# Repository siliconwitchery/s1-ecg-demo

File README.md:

# S1 ECG Reference Kit

**Features:**

- Single chip frontend based on the [AD8233](https://www.analog.com/en/products/ad8233.html)
- S1 Module with Bluetooth 5.2 and FPGA
- Integrated lithium battery
- Ultra low power auto-sleep down to 175uA
- Open source design

**Applications:**

- Learning and teaching around heart health
- Research of ML based ECG algorithms
- Wireless ECG data logging
- New product development

A powerful analog frontend combined with the S1 Module makes this an all-in-one kit to deploy and test algorithms with ease. Be that for learning, research, or as the starting point for your next product.

<br>

<br>

## Get the hardware

**Order the S1 ECG Kit from [Digi-Key](https://www.digikey.com/en/products/detail/silicon-witchery/S1-ECG-KIT/15926538) 🛍**

You're also free to build your own hardware using the design files in this repository. Everything is open source and ready to build upon.

- [Schematic](https://github.com/siliconwitchery/s1-ecg-demo/blob/main/schematic.pdf)
- [Gerber files](https://github.com/siliconwitchery/s1-ecg-demo/tree/main/gerber-files/factory-version)
- [Bill of materials](https://github.com/siliconwitchery/s1-ecg-demo/blob/main/bill-of-materials.pdf)

The design is produced in [KiCad v6.0.1](https://www.kicad.org/download/).

## Building the code

The S1 ECG reference kit uses a three probe measurement to determine heart activity. By holding the board with both hands, the device automatically wakes from sleep, and begins calibrating the amplifier sensitivity. After a few seconds, you will see your pulse displayed on the LED bar graph. Letting go of the terminals puts the system back into sleep mode.

The base firmware is highly expandable and a perfect starting point for new designs. To get started, begin by cloning this repository.

``` bash
git clone --recurse-submodules https://github.com/siliconwitchery/s1-ecg-demo.git
cd s1-ecg-demo
```

If you haven't already, set up these [tools](https://github.com/siliconwitchery/s1-sdk/blob/main/README.md#setting-up-the-tools) in order to build the project.

You should then be able to run `make`. *Be sure to include the path to your NRF SDK folder*.

``` bash
make -C firmware build-verilog NRF_SDK_PATH=${HOME}/nRF5_SDK
make -C firmware flash NRF_SDK_PATH=${HOME}/nRF5_SDK
```

The first `make` command will build the Verilog project, and convert the binary file into a header file. The nRF application transfers this binary to the FPGA after boot up. In your application, you could download this binary dynamically over Bluetooth rather than storing it within the flash of the nRF chip.

The second `make` command builds the nRF code, and flashes the module using a J-Link debugger. You can also use an [nRF52 devkit](https://www.nordicsemi.com/Products/Development-hardware/nrf52-dk), or [JLink Edu Mini](https://www.digikey.se/product-detail/en/segger-microcontroller-systems/8-08-91-J-LINK-EDU-MINI/899-1061-ND/7387472) along with and [this](https://www.tag-connect.com/product/tc2030-ctx-nl-6-pin-no-legs-cable-with-10-pin-micro-connector-for-cortex-processors) 6pin cable to flash your board.

Once you're up and running, you can begin customizing the application to your needs. Be sure to visit our documentation center to learn more about the S1 Module, as well as its features.

## Measuring sleep current

The board features a jumper disconnect to allow for the battery current to be directly measured. During sleep modes, this can be configured down to as low as 175uA or less, depending on the sleep state needed.

Note that if the USB-C power cable is plugged in while measuring, the charge current to the battery will be measured rather than the discharge current.

## Sensitivity of the ECG amplifier and EMI

The ECG amplifier is designed to pick up the tiny signals across your hands. It's therefore quite sensitive to external interference. Operation solely from the lithium battery is ideal. Here the board remains isolated from other noise sources and accurate measurements can be made.

Certain USB-C charges can induce a lot of EMI and ground loops can be created via the users hands. This may create noise in the measurement so it's worth keeping in mind when developing or logging data.

## Looking after the battery

**Lithium batteries are of course dangerous if improperly handled.** The S1 module features safety checks to avoid damage and such damage is unlikely. However it is possible to misconfigure the integrated power management IC to overcharge/undercharge or charge the lithium battery with too much current.

It is recommended to only use the battery configuration provided in this example to ensure safety and lifetime of the lithium battery.

If in doubt, it is possible to simply remove the battery current measurement jumper, and this will disconnect the battery from the system.

## Bugs and improvements

If you have any questions, or if something is unclear, feel free to create an [issue](https://github.com/siliconwitchery/s1-ecg-demo/issues) and we'll try our best to improve it.

## Licence

Copyright 2022 © Silicon Witchery.

This design is licenced under: [CERN Open Hardware Licence Version 2 - Permissive](https://ohwr.org/cern_ohl_p_v2.pdf).

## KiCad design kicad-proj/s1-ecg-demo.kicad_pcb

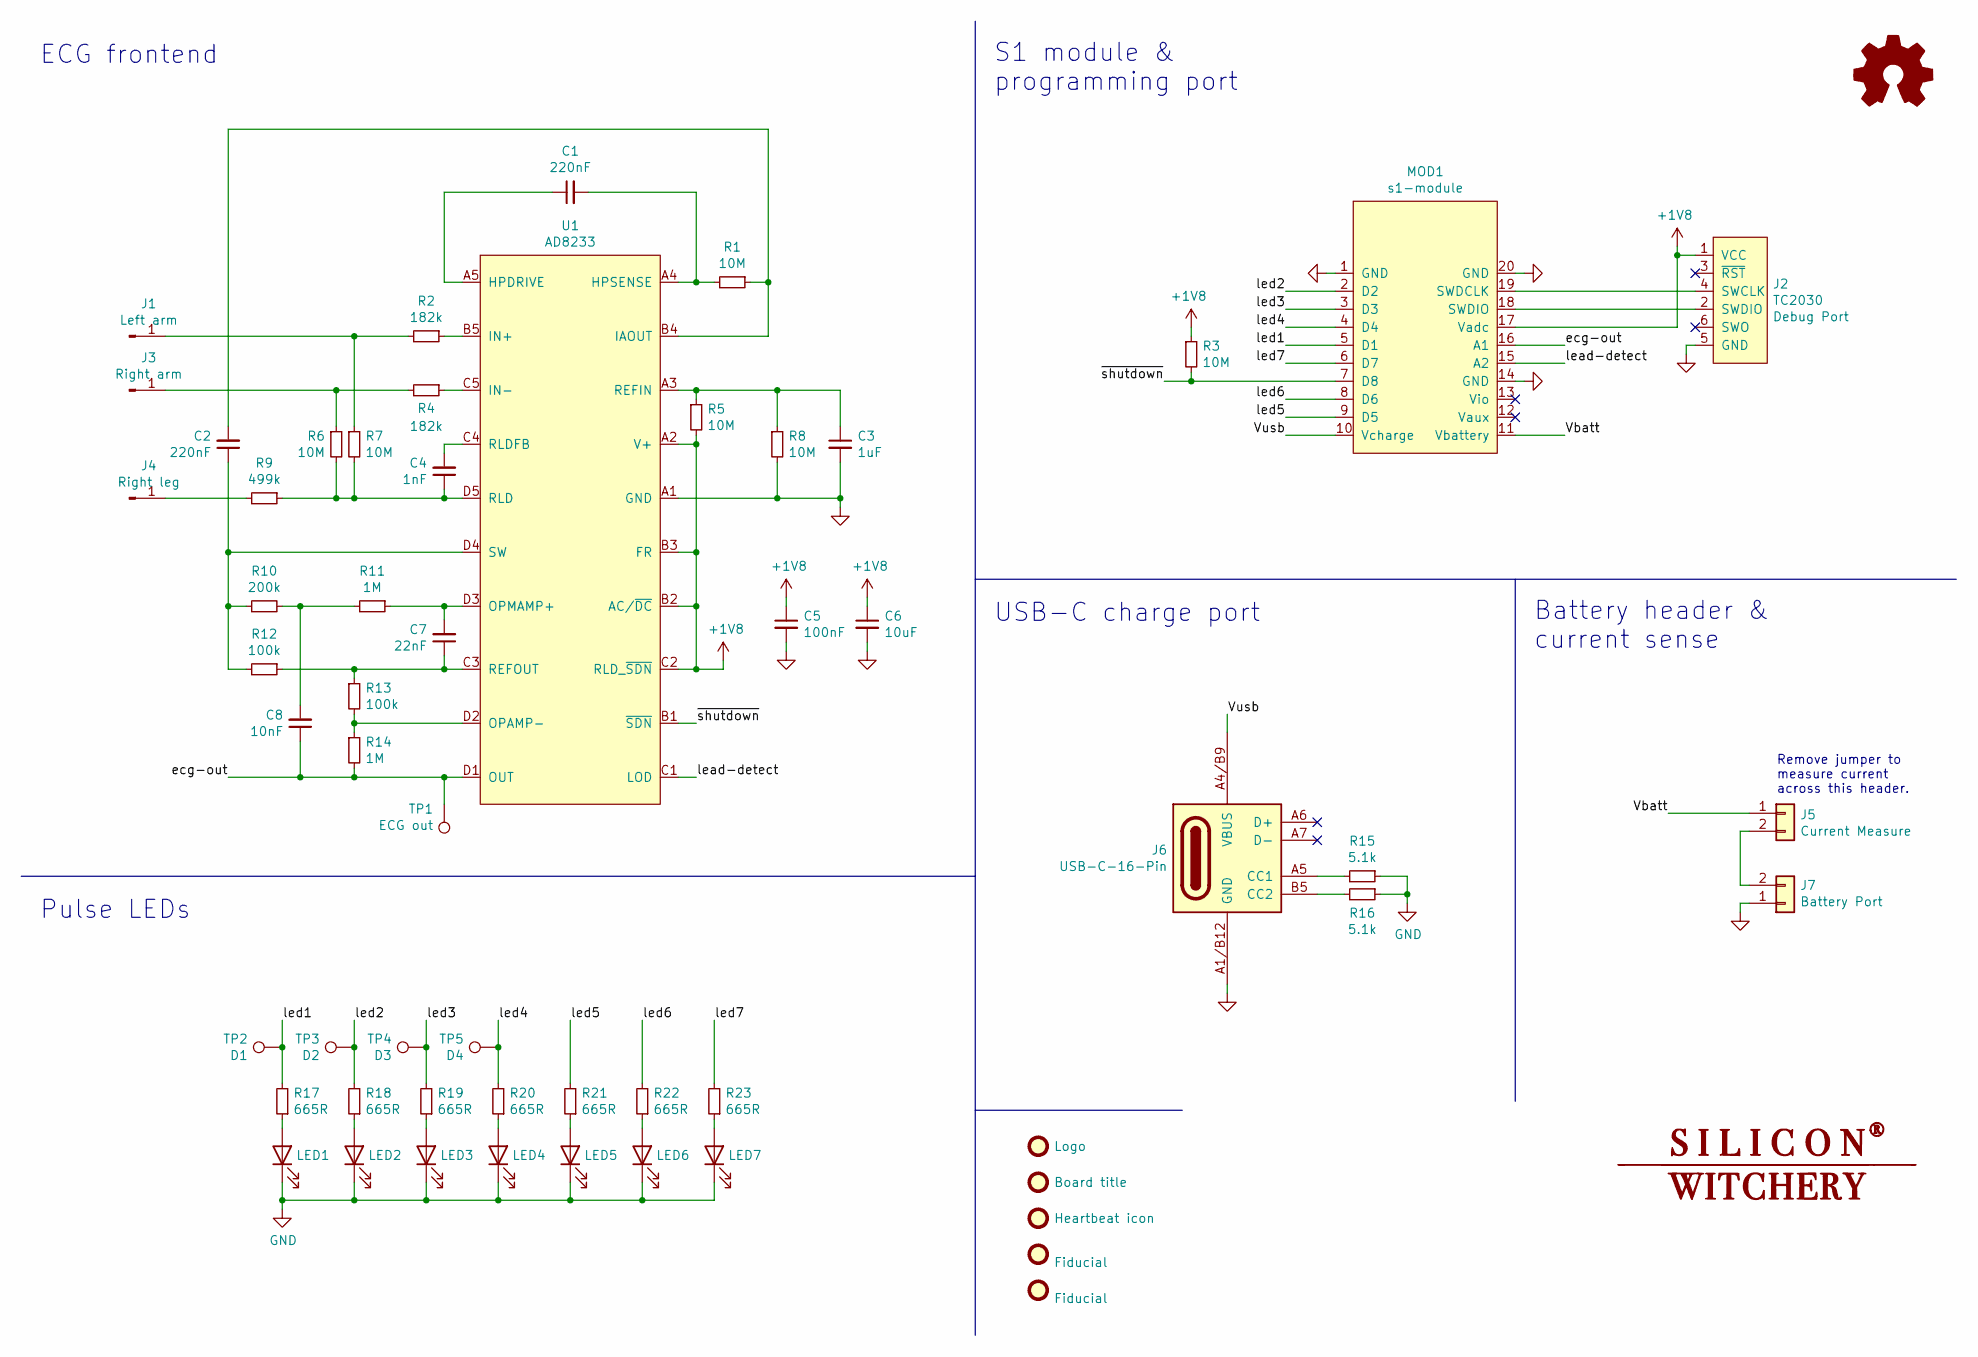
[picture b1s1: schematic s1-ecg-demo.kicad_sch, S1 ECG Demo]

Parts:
C1, C2: 220nF; C_0402_1005Metric
C3: 1uF; C_0402_1005Metric
C4: 1nF; C_0402_1005Metric
C5: 100nF; C_0402_1005Metric
C6: 10uF; C_0402_1005Metric
C7: 22nF; C_0402_1005Metric
C8: 10nF; C_0402_1005Metric
FID1: Logo; sw-logo
FID2: Board title; title
FID3: Heartbeat icon; heartbeat
FID4, FID5: Fiducial; Fiducial_0.5mm_Mask1mm
J1: Left arm; ECG-pad
J2: TC2030; Tag-Connect_TC2030-IDC-NL_2x03_P1.27mm_Vertical
J3: Right arm; ECG-pad
J4: Right leg; ECG-pad
J5: Current Measure; Conn_2_SMD_2.54mm
J6: USB-C-16-Pin; DX07S016JA1R1500
J7: Battery Port; Conn_2_SMD_2.54mm
LED1, LED2, LED3, LED4, LED5, LED6, LED7: LED; LED_0603_1608Metric
MOD1: s1-module
R1, R3, R5, R6, R7, R8: 10M; R_0201_0603Metric
R2, R4: 182k; R_0201_0603Metric
R9: 499k; R_0201_0603Metric
R10: 200k; R_0201_0603Metric
R11, R14: 1M; R_0201_0603Metric
R12, R13: 100k; R_0201_0603Metric
R15, R16: 5.1k; R_0201_0603Metric
R17, R18, R19, R20, R21, R22, R23: 665R; R_0201_0603Metric
TP1: ECG out; TestPoint_Pad_D1.0mm
TP2: D1; TestPoint_Pad_D1.0mm
TP3: D2; TestPoint_Pad_D1.0mm
TP4: D3; TestPoint_Pad_D1.0mm
TP5: D4; TestPoint_Pad_D1.0mm
U1: AD8233; WLCSP-20

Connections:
+1V8: C5.1, C6.1, J2.1 (VCC), MOD1.17 (Vadc), R3.1, R5.2, U1.A2 (V+), U1.B2 (AC/~DC), U1.B3 (FR), U1.C2 (RLD_~SDN)
/Vbatt: J5.1, MOD1.11 (Vbattery)
/ecg-out: C8.1, MOD1.16 (A1), R14.2, TP1.1, U1.D1 (OUT)
/lead-detect: MOD1.15 (A2), U1.C1 (LOD)
/led1: MOD1.5 (D1), R17.2, TP2.1
/led2: MOD1.2 (D2), R18.2, TP3.1
/led3: MOD1.3 (D3), R19.2, TP4.1
/led4: MOD1.4 (D4), R20.2, TP5.1
/led5: MOD1.9 (D5), R21.2
/led6: MOD1.8 (D6), R22.2
/led7: MOD1.6 (D7), R23.2
/~shutdown: MOD1.7 (D8), R3.2, U1.B1 (~SDN)
GND: C3.2, C5.2, C6.2, J2.5 (GND), J6.A1/B12 (GND), J6.A12/B1 (GND), J7.1, LED1.1 (K), LED2.1 (K), LED3.1 (K), LED4.1 (K), LED5.1 (K), LED6.1 (K), LED7.1 (K), MOD1.1 (GND), MOD1.14 (GND), MOD1.20 (GND), R8.2, R15.1, R16.1, U1.A1 (GND)
unnamed: C1.1, U1.A5 (HPDRIVE)
unnamed: C1.2, R1.2, U1.A4 (HPSENSE)
unnamed: C2.1, R10.1, R12.2, U1.D4 (SW)
unnamed: C2.2, R1.1, U1.B4 (IAOUT)
unnamed: C3.1, R5.1, R8.1, U1.A3 (REFIN)
unnamed: C4.1, R6.2, R7.2, R9.1, U1.D5 (RLD)
unnamed: C4.2, U1.C4 (RLDFB)
unnamed: C7.1, R12.1, R13.1, U1.C3 (REFOUT)
unnamed: C7.2, R11.1, U1.D3 (OPMAMP+)
unnamed: C8.2, R10.2, R11.2
unnamed: J1.1, R2.2, R7.1
unnamed: J2.2 (SWDIO), MOD1.18 (SWDIO)
unnamed: J2.4 (SWCLK), MOD1.19 (SWDCLK)
unnamed: J3.1, R4.2, R6.1
unnamed: J4.1, R9.2
unnamed: J5.2, J7.2
unnamed: J6.A5 (CC1), R15.2
unnamed: J6.B5 (CC2), R16.2
unnamed: LED1.2 (A), R17.1
unnamed: LED2.2 (A), R18.1
unnamed: LED3.2 (A), R19.1
unnamed: LED4.2 (A), R20.1
unnamed: LED5.2 (A), R21.1
unnamed: LED6.2 (A), R22.1
unnamed: LED7.2 (A), R23.1
unnamed: R2.1, U1.B5 (IN+)
unnamed: R4.1, U1.C5 (IN-)
unnamed: R13.2, R14.1, U1.D2 (OPAMP-)
VBUS: J6.A4/B9 (VBUS), J6.A9/B4 (VBUS), MOD1.10 (Vcharge)

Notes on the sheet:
Battery header & current sense
USB-C charge port
S1 module & programming port
ECG frontend
Remove jumper to measure current across this header.
Pulse LEDs

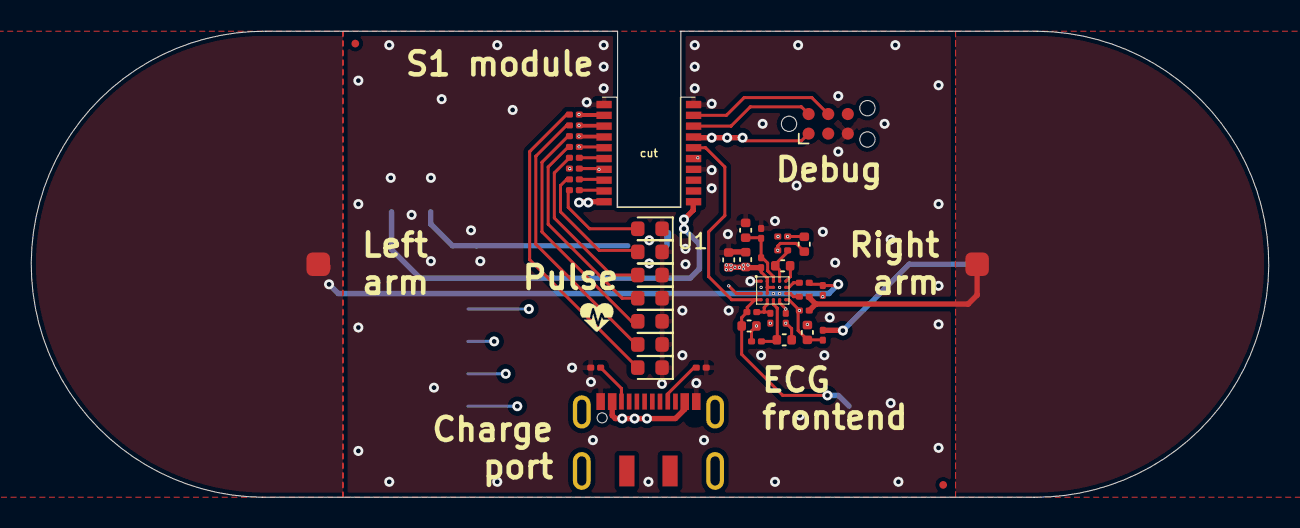
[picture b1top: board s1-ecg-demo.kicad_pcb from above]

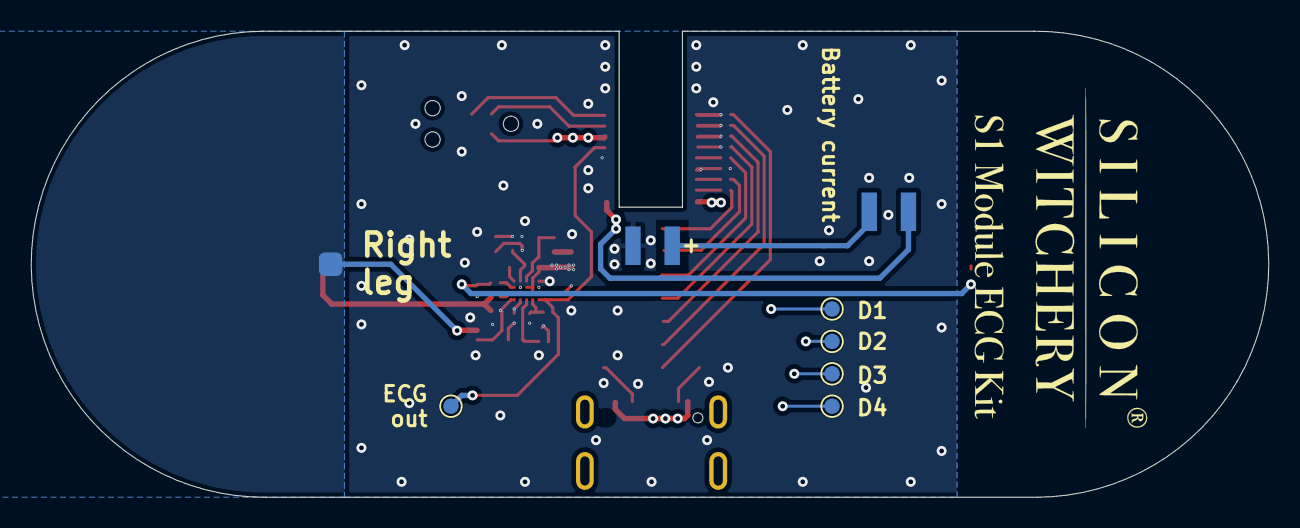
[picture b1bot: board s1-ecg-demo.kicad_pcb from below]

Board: 4 copper layers, 80.2 x 30.2 mm, 57 parts (10 on the bottom side), 42 nets.

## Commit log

2021-08-10 Initial
2021-08-10 added schematic
2021-08-10 added BOM
2021-08-12 Updated LEDs and BOM
2021-08-13 updated to match eval board
2021-08-16 pill shape, nearly done routing
2021-08-17 Layout complete, needs checking
2021-08-18 Final check done
2021-08-18 initial firmware
2021-08-18 removed submodule
2021-08-18 modified tasks to include paths
2021-08-18 readme
2021-08-18 end of day 18-08
2021-08-18 Little bit of clean up fixed battery and current header re-exported gerbers
2021-08-19 Final files ready for order
2021-08-19 Simple FIR filter works on ADC data
2021-08-20 SPI tx to fpga works
2021-08-20 1 pin pwm works
2021-08-23 Added factory gerber files
2021-08-26 ecg on led display is ok, auto sdn on leads off
2021-08-26 included s1-sdk changes
2021-08-27 temp
2021-08-27 added main.h
2021-08-27 formatting
2021-08-27 io extender temp
2021-08-31 New BOM added
2021-08-31 BOM and disclaimer updated Added kicad ebom
2021-08-31 added PDF bom
2021-09-13 basic low power mode works
2021-09-16 "quick startup" works
2021-09-20 lpm stepped test
2021-09-22 testing lpm now at 170uA
2021-09-30 fixed small bugs for mac
2021-10-01 added def for stepped sleep mode
2021-10-01 docs edit
2021-10-01 cleanup
2021-10-01 added readme
2021-10-01 added schematic pdf
2021-10-13 Added shutdown pullup resistor Adjusted current probe header location Updated BOM Exported v2 gerber
2021-10-13 Fixed ground break Isolation around battery positive terminal Removed the cuttable jumper Cleaned up silkscreen Added 0.1" pin jumper to BOM
2021-10-13 Updated BOM layout
2021-10-13 removed ibom
2021-10-14 fixed link
2021-10-14 migrated to new SDK layout
2021-10-14 removed settings vscode file
2021-10-14 removed another vscode folder
2021-10-14 Updated the vs code files which are nice to have in the repo
2021-10-15 Updated to latest SDK branch on main Added back fir filter reference image
2021-10-15 fixed makefile template
2021-10-15 refactor
2021-10-19 Latest SDK
2021-10-27 fixed flash in task.json and updated s1-sdk spi
2021-10-28 added battery spec added factory stencil gerber
2021-10-28 Uploaded latest production gerber from factory
2021-11-30 added pmic charge en
2021-12-02 Cleaned up templates
2021-12-02 Moved to new SDK, cleaned up logs and unused code
2022-01-28 Migrated to Kicad 6 Re-exported gerbers with correct WLCSP paste layer
2022-01-28 Rev 3 PCB Release Only change is the WLCSP solder paste size
2022-01-28 Added battery label files
2022-01-28 Updated readme with digikey order link
2022-01-28 Updated order link
2022-06-20 Updated files for latest SDK release
2022-12-12 Replaced licence with CERN OHL-P-v2

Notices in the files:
kicad-proj/s1-ecg-demo.kicad_pcb:
Licenced under: CERN OHL-P-v2
